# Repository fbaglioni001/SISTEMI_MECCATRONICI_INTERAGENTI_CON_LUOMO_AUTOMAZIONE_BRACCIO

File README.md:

# SISTEMI_MECCATRONICI_INTERAGENTI_CON_LUOMO_AUTOMAZIONE_BRACCIO

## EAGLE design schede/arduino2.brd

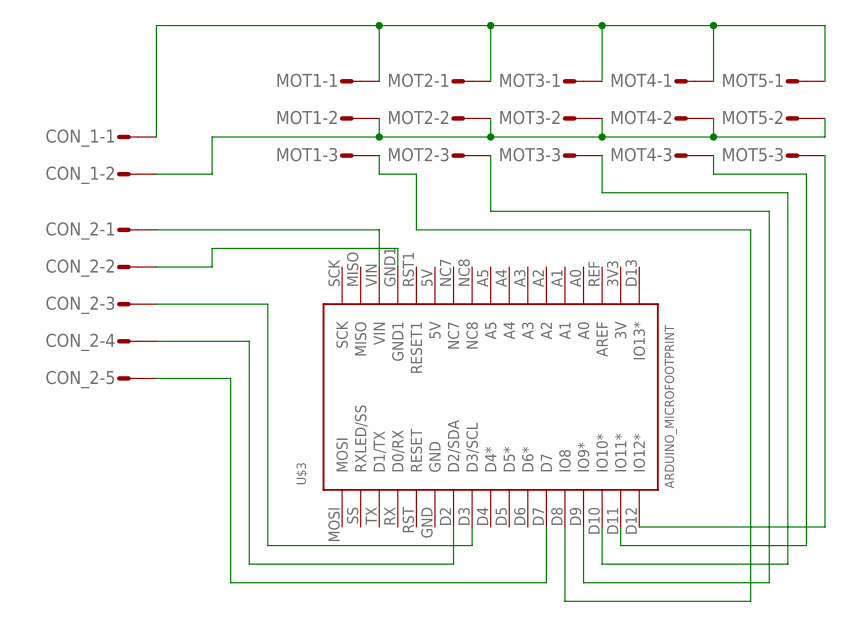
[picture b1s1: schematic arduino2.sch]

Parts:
CON_1: S02P
CON_2: S05P
MOT1, MOT2, MOT3, MOT4, MOT5: S03P
U$3: ARDUINO_MICROFOOTPRINT; ARDUINO-MICRO

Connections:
unnamed: CON_1.1, MOT1.1, MOT2.1, MOT3.1, MOT4.1, MOT5.1
unnamed: CON_1.2, MOT1.2, MOT2.2, MOT3.2, MOT4.2, MOT5.2
unnamed: CON_2.1, U$3.VIN
unnamed: CON_2.2, U$3.GND1
unnamed: CON_2.3, U$3.D3 (D3/SCL)
unnamed: CON_2.4, U$3.D2 (D2/SDA)
unnamed: CON_2.5, U$3.D7
unnamed: MOT5.3, U$3.D12 (IO12*)
unnamed: MOT4.3, U$3.D11 (IO11*)
unnamed: MOT3.3, U$3.D10 (IO10*)
unnamed: MOT2.3, U$3.D9 (IO9*)
unnamed: MOT1.3, U$3.D8 (IO8)

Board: 2 copper layers, 8 parts (0 on the bottom side), 12 nets, no tracks yet.

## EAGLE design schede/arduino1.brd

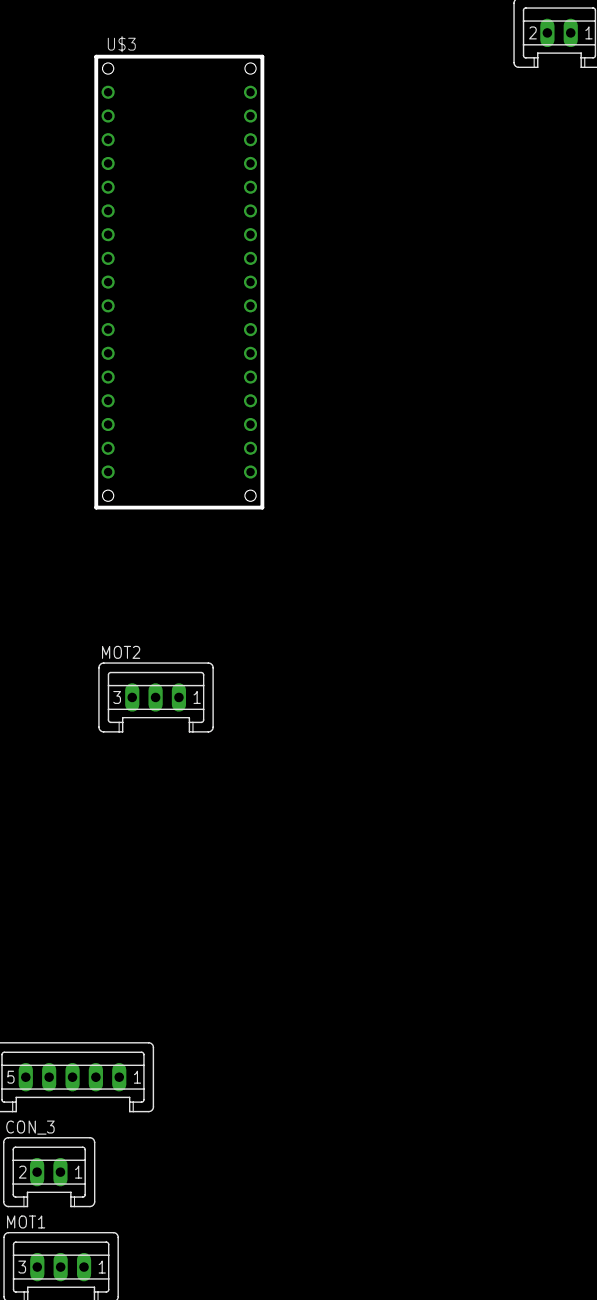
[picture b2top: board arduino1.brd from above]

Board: 2 copper layers, 17.8 x 48.3 mm, 6 parts (0 on the bottom side), 7 nets, no tracks yet.

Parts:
CON_1, CON_3: S02P
CON_2: S05P
MOT1, MOT2: S03P
U$3: ARDUINO_MICROFOOTPRINT; ARDUINO-MICRO

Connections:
GND: CON_3.2, U$3.GND1
HV: CON_3.1, U$3.VIN
unnamed: CON_1.1, MOT1.3, MOT2.3
unnamed: CON_1.2, MOT1.2, MOT2.2
unnamed: MOT2.1, U$3.D11
unnamed: MOT1.1, U$3.D12
unnamed: CON_2.5, U$3.D7

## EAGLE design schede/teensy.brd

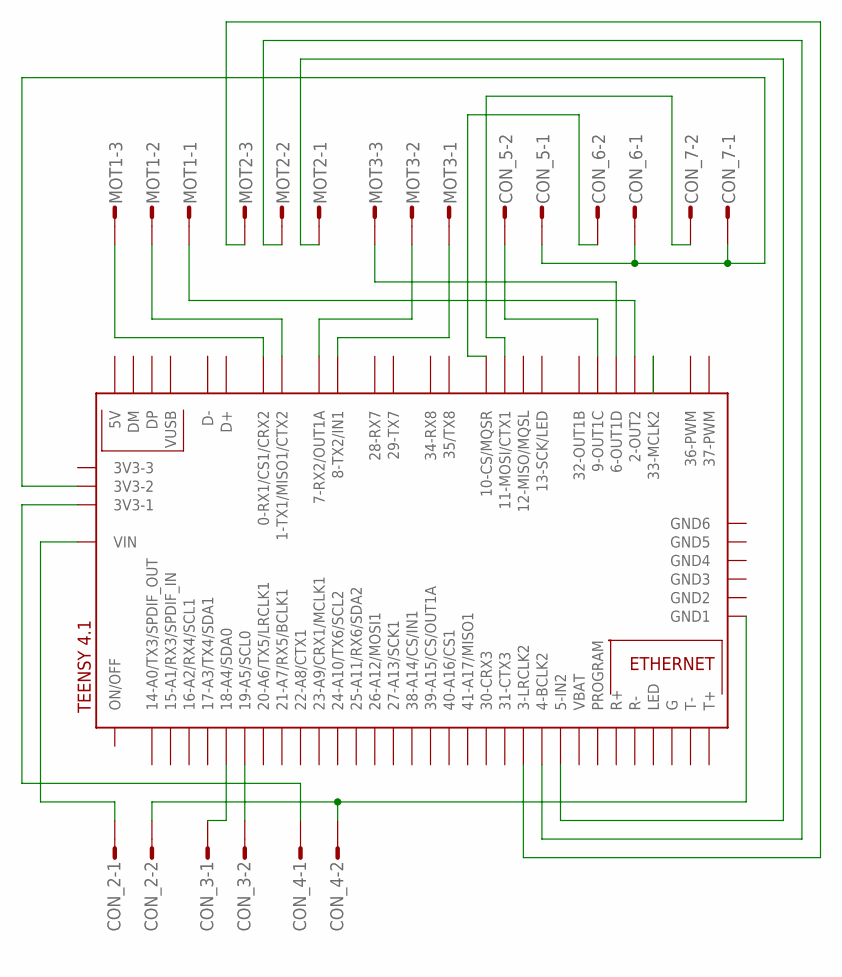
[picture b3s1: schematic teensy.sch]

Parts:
CON_2, CON_3, CON_4, CON_5, CON_6, CON_7: S02P
MOT1, MOT2, MOT3: S03P
U$1: TEENSY41

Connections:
unnamed: CON_2.1, U$1.VIN
unnamed: CON_4.1, U$1.3V3-1
unnamed: CON_2.2, CON_4.2, U$1.GND1
unnamed: CON_5.1, CON_6.1, CON_7.1, U$1.3V3-2
unnamed: MOT1.3, U$1.0-RX1/CS1/CRX2
unnamed: MOT1.2, U$1.1-TX1/MISO1/CTX2
unnamed: MOT1.1, U$1.2-OUT2
unnamed: MOT3.2, U$1.7-RX2/OUT1A
unnamed: MOT3.1, U$1.8-TX2/IN1
unnamed: CON_3.1, U$1.18-A4/SDA0
unnamed: CON_3.2, U$1.19-A5/SCL0
unnamed: MOT3.3, U$1.6-OUT1D
unnamed: CON_5.2, U$1.9-OUT1C
unnamed: CON_6.2, U$1.10-CS\MQSR (10-CS/MQSR)
unnamed: CON_7.2, U$1.11-MOSI/CTX1
unnamed: MOT2.3, U$1.3-LRCLK2
unnamed: MOT2.2, U$1.4-BCLK2
unnamed: MOT2.1, U$1.5-IN2

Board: 2 copper layers, 10 parts (0 on the bottom side), 18 nets, no tracks yet.

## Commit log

2021-11-14 hand_controller
2021-11-14 Avanzamento con il codice della mano
    Il codice sembra funzionare, manca testare sul campo con la mano.
2021-11-24 Update robotic_hand_controller
2021-11-24 init .ino arm and wrist controller
2021-11-24 robohand
2021-12-02 wrist
2022-03-31 Motor classe funziona
2022-04-01 prova implemantazione timer interrupt per evitare problemi di timing
2022-04-02 modifiche
2022-04-02 relazione e Matlab
2022-04-04 start i2c
2022-04-08 home
2022-04-10 homing
2022-04-20 test
2022-04-22 mano e polso
2022-04-26 qjdjaj
2022-04-26 i2c correct
2022-04-26 caricamento programmi
2022-04-26 ros update
2022-04-27 Ros is setting up (to try the system: sudo -s -> roslaunch robotic_arm test_system.launch)
2022-04-27 end working 27-04-2022
2022-04-28 cor1
2022-04-28 cambiamenti Ros
2022-04-28 fine lavori pomeriggio
2022-05-01 3tratti law
2022-05-01 motion law test
2022-05-10 schede elettriche
2022-06-06 meccanica
